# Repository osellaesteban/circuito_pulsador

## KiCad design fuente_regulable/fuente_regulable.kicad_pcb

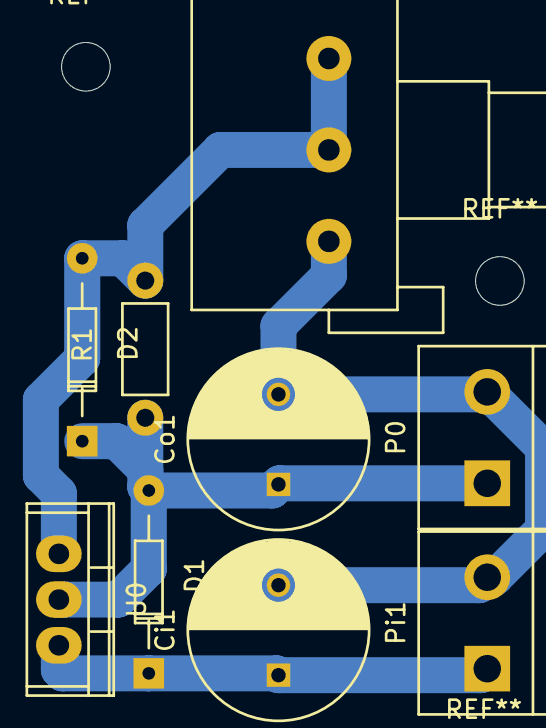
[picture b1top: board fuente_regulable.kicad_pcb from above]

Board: 2 copper layers, 9 parts (0 on the bottom side), 4 nets.

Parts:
Ci1: 0.1uF; C_Radial_D10_L20_P5
Co1: 10uF; C_Radial_D10_L20_P5
D1, D2: FR107; Diode_DO-35_SOD27_Horizontal_RM10
P0: CONN_01X02; bornier2
Pi1: CONN_01X02; bornier2
R1: 240; Resistor_Horizontal_RM7mm
RV1: 10; Potentiometer_Alps-RK163-single_15mm
U0: LM317AT; TO-220

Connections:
unnamed: Ci1.1, D1.1, Pi1.1, U0.3
unnamed: Ci1.2, Co1.2, P0.2, Pi1.2, RV1.1
unnamed: Co1.1, D1.2, D2.1, P0.1, R1.1, U0.2
unnamed: D2.2, R1.2, RV1.2, RV1.3, U0.1

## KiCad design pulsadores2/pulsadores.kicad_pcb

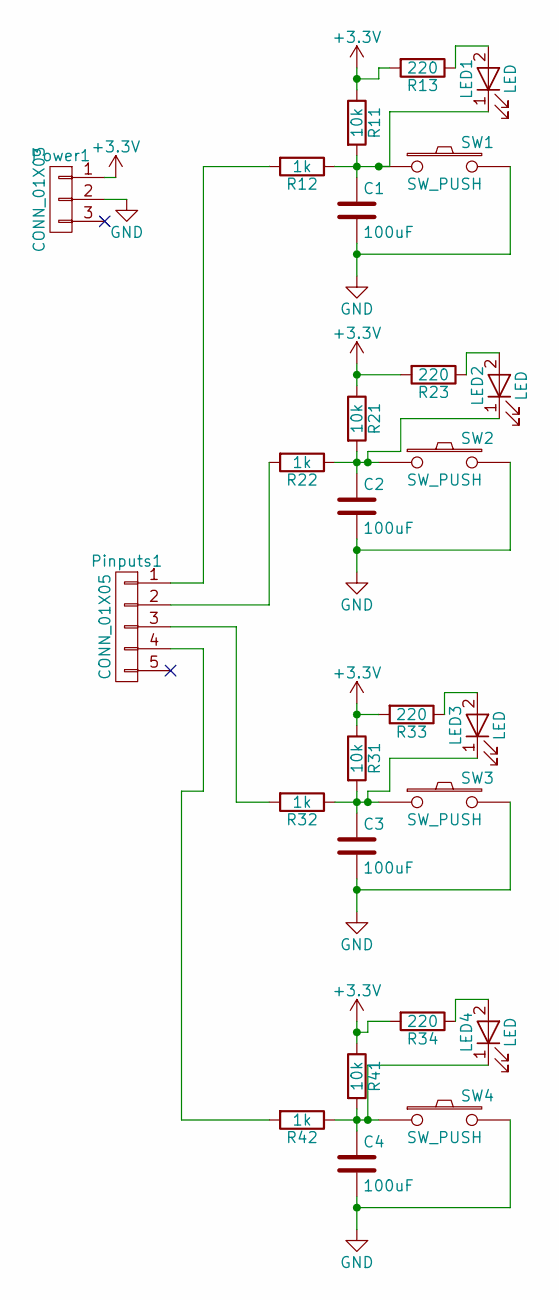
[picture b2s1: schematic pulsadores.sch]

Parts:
C1, C2, C3, C4: 100uF; C_Disc_D3_P2.5
LED1, LED2, LED3, LED4: LED; LED_D3.0mm_Horicontal_O1.27mm
Pinputs1: CONN_01X05; Pin_Header_Straight_1x05
Power1: CONN_01X03; Pin_Header_Angled_1x03
R11, R21, R31, R41: 10k; Resistor_Horizontal_RM7mm
R12: 1k; R_Box_L8.4mm_W2.5mm_P5.08mm
R13, R23, R33, R34: 220; R_Box_L8.4mm_W2.5mm_P5.08mm
R22, R32, R42: 1k; Resistor_Horizontal_RM7mm
SW1, SW2, SW3, SW4: SW_PUSH; Push_E-Switch_KS01Q01

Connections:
+3V3: Power1.1, R11.1, R13.2, R21.1, R23.2, R31.1, R33.2, R34.2, R41.1
GND: C1.2, C2.2, C3.2, C4.2, Power1.2, SW1.2, SW2.2, SW3.2, SW4.2
unnamed: C1.1, LED1.1 (K), R11.2, R12.1, SW1.1
unnamed: C2.1, LED2.1 (K), R21.2, R22.1, SW2.1
unnamed: C3.1, LED3.1 (K), R31.2, R32.1, SW3.1
unnamed: C4.1, LED4.1 (K), R41.2, R42.1, SW4.1
unnamed: LED1.2 (A), R13.1
unnamed: LED2.2 (A), R23.1
unnamed: LED3.2 (A), R33.1
unnamed: LED4.2 (A), R34.1
unnamed: Pinputs1.1, R12.2
unnamed: Pinputs1.2, R22.2
unnamed: Pinputs1.3, R32.2
unnamed: Pinputs1.4, R42.2

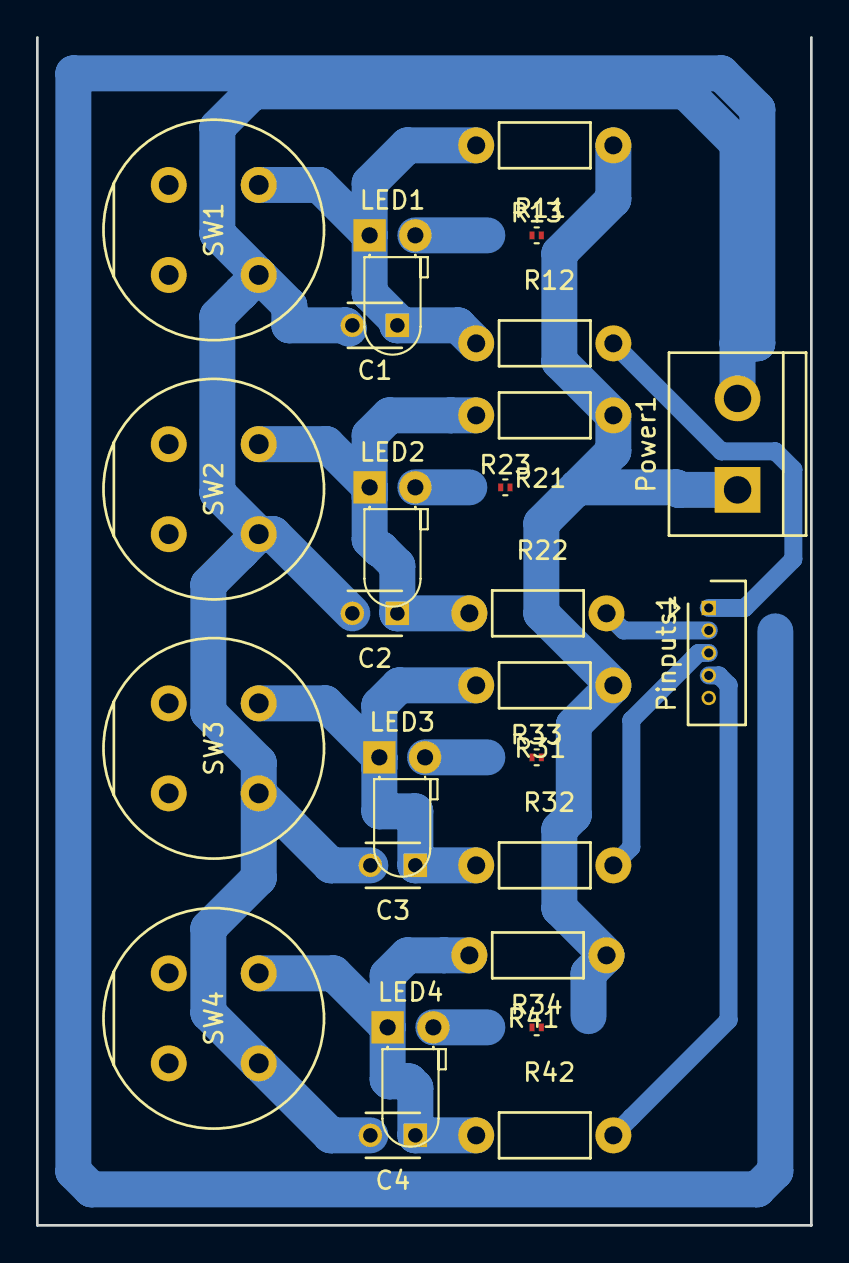
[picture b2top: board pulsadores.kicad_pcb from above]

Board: 2 copper layers, 43.0 x 66.0 mm, 26 parts (0 on the bottom side), 14 nets.

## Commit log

2017-07-20 primer carga
